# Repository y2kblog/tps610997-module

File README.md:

# TPS610997 超低消費電力 5V出力昇圧モジュール

## 概要

超低消費電力の5V出力昇圧型DC-DCコンバータ TPS610997 (Texas Instruments Inc.製) を搭載したモジュールです。  
TPS610997の**静止電流は約1μA程度**と非常に低く、また**0.7Vから動作**するため、コイン電池1個、もしくはアルカリ／ニカド／ニッケル水素乾電池1～2本で駆動するアプリケーションに適しています。  
さらに、TPS610997は**イネーブルピンによりシャットダウンが可能**であり、シャットダウン時は負荷が入力電源から切断されるため消費電流を低減できます。

### 仕様
- 入力電圧：0.7V～5.5V
- 出力電圧：5V (軽負荷時：5.15V)
- 最大出力電流：300mA（3.3V入力時）
  ※最大出力電流は入力電圧と効率に依存します
- 静止電流：1μA (軽負荷時)
- イネーブルピン付き（ENピンをVinピンに接続すると5V昇圧機能が有効化されます）
- 効率
  - 75% (入力電圧3.3V、負荷10μA)
  - 93% (入力電圧3.3V、負荷200mA)
- 基板サイズ：10mm × 6.35mm
- ピン間隔：2.54mm

## 販売  
[スイッチサイエンス委託販売ページ](https://www.switch-science.com/catalog/6505/)  
※大量注文や在庫に関する問い合わせは[こちら](mailto:info.y2kb@gmail.com)までご連絡ください。  

### 回路図  

## 性能評価  

### 消費電流 (シャットダウン時 / 負荷100kΩ時 / 負荷1kΩ時)

## データシート  
[TPS61099xデータシート(日本語)](https://www.tij.co.jp/jp/lit/gpn/tps61099)

## License
MIT License

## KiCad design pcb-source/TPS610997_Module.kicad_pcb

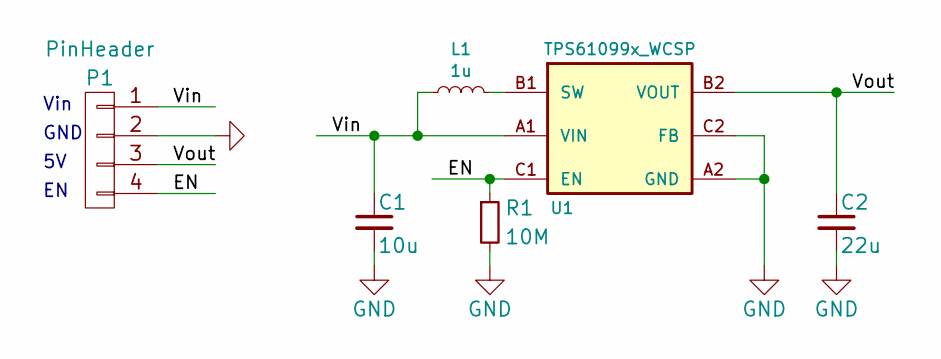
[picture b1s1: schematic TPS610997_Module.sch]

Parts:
C1: 10u; C_0603
C2: 22u; C_0805
L1: 1u; L_0805
P1: PinHeader; USER_SIL-4_NoSilk
R1: 10M; R_0603
U1: TPS61099x_WCSP; USER_Boost_TPS61099x_WCSP

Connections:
/EN: P1.4, R1.1, U1.C1 (EN)
/Vin: C1.1, L1.1, P1.1, U1.A1 (VIN)
/Vout: C2.1, P1.3, U1.B2 (VOUT)
GND: C1.2, C2.2, P1.2, R1.2, U1.A2 (GND), U1.C2 (FB)
unnamed: L1.2, U1.B1 (SW)

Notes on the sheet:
GND
Vin

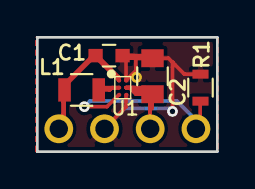
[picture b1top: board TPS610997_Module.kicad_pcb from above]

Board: 2 copper layers, 10.0 x 6.3 mm, 6 parts (0 on the bottom side), 5 nets.

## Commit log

2020-08-02 add purchase page link
2020-10-14 add EN pin description
